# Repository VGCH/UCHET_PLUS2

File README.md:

## Проект устройства для интеграции счетчиков воды в системы умного дома

Принципиальная схема

Полное описание в статье на Хабр

[Ссылка на статью ](https://habr.com/ru/articles/827248/)

Если данный проект был вам полезен, то вы можете задонатить разработчику на оборудование. 

[Ссылка на донат](https://dalink.to/cyberex_tech)

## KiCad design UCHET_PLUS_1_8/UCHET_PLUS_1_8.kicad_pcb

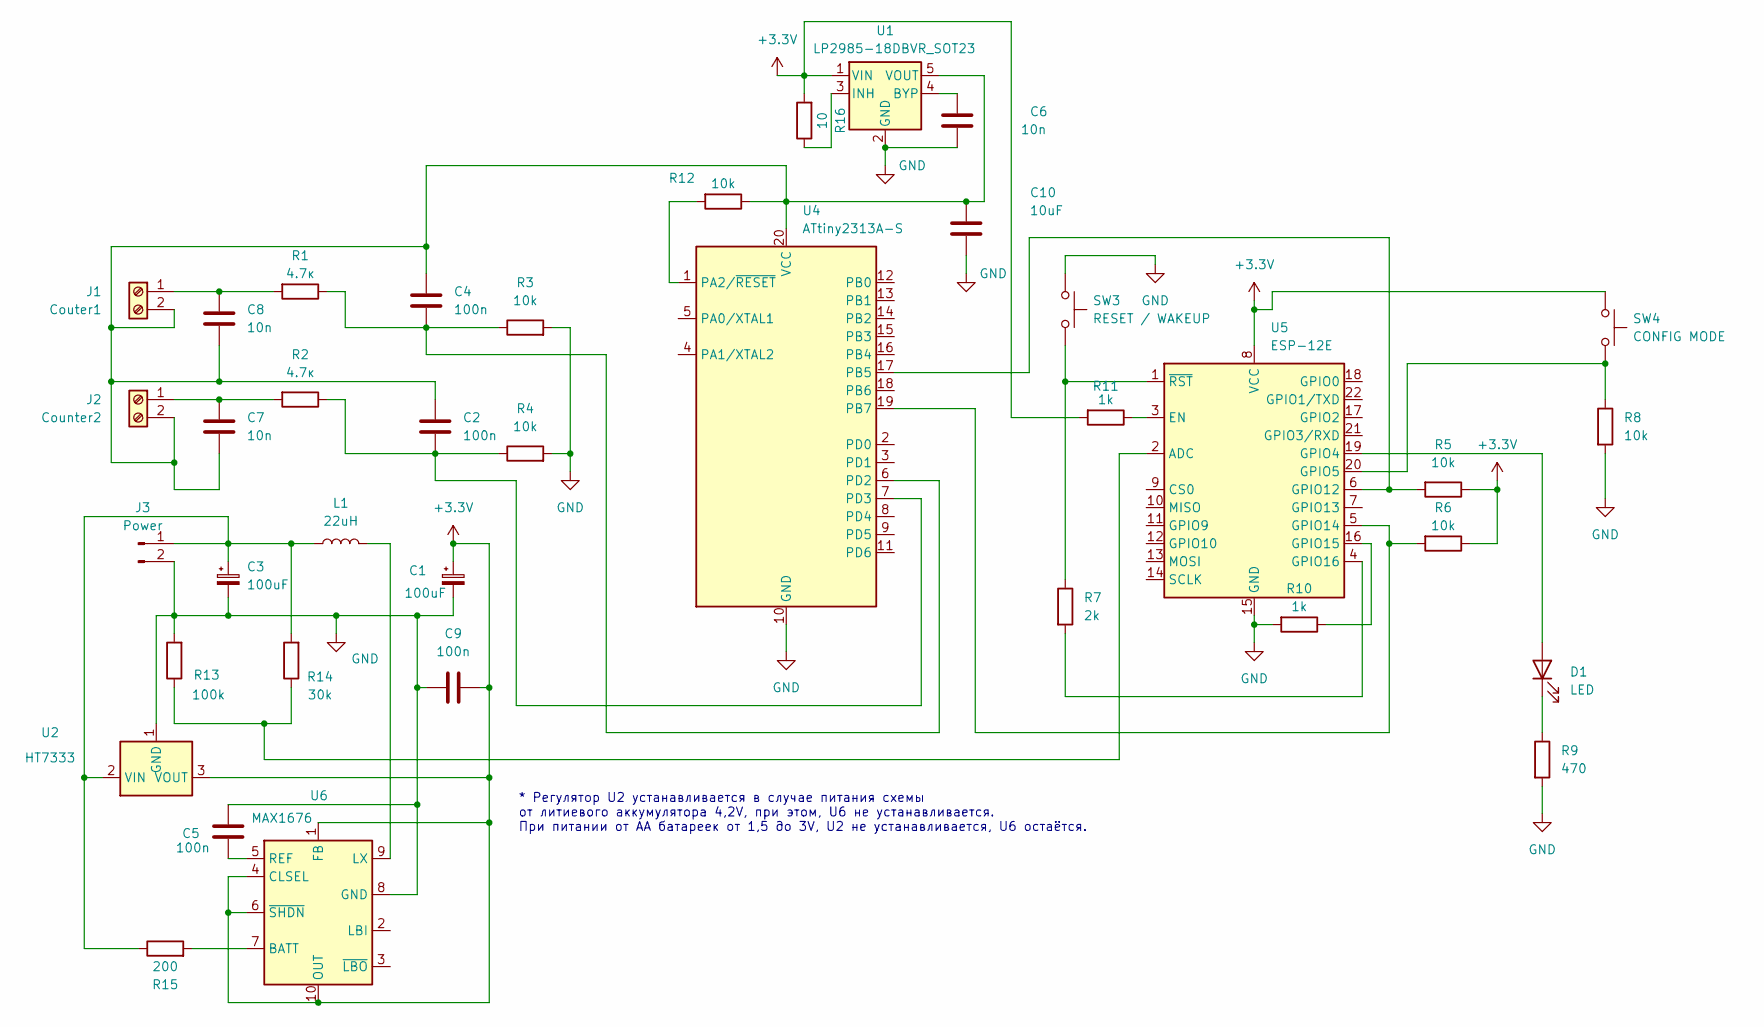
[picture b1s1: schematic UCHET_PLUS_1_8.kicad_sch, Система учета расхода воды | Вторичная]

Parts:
C1, C3: 100uF; CP_Elec_6.3x5.8
C2, C4, C5, C9: 100n; C_1206_3216Metric
C6, C7, C8: 10n; C_1206_3216Metric
C10: 10uF; C_1206_3216Metric
D1: LED; LED_D3.0mm_IRGrey
J1: Couter1; TerminalBlock_MetzConnect_Type101_RT01602HBWC_1x02_P5.08mm_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
J2: Counter2; TerminalBlock_MetzConnect_Type101_RT01602HBWC_1x02_P5.08mm_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
J3: Power; TerminalBlock_4Ucon_1x02_P3.50mm_Horizontal
L1: 22uH; L_1210_3225Metric
R1, R2: 4.7к; R_0805_2012Metric
R3, R4, R5, R6, R8, R12: 10k; R_0805_2012Metric
R7: 2k; R_0805_2012Metric
R9: 470; R_0805_2012Metric
R10, R11: 1k; R_0805_2012Metric
R13: 100k; R_0805_2012Metric
R14: 30k; R_0805_2012Metric
R15: 200; R_0805_2012Metric
R16: 10; R_0805_2012Metric
SW3: RESET / WAKEUP; SW_PUSH_6mm
SW4: CONFIG MODE; SW_PUSH_6mm
U1: LP2985-18DBVR_SOT23; SOT-23-5
U2: HT7333; SOT-23
U4: ATtiny2313A-S; SOIC-20W_7.5x12.8mm_P1.27mm
U5: ESP-12E
U6: MAX1676; MSOP-10-1EP_3x3mm_P0.5mm_EP2.2x3.1mm_Mask1.83x1.89mm_Therma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

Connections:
+3.3V: C1.1, C9.1, R5.1, R6.1, R11.2, R16.2, SW4.1, U1.1 (VIN), U2.3 (VOUT), U5.8 (VCC), U6.1 (FB), U6.4 (CLSEL), U6.6 (~SHDN), U6.10 (OUT), U6.11 (GND); also elsewhere on the board
GND: C1.2, C3.2, C5.1, C6.2, C9.2, C10.2, J3.2, R3.2, R4.2, R8.2, R9.2, R10.2, R13.2, SW3.1, U1.2 (GND), U2.1 (GND), U4.10 (GND), U5.15 (GND), U6.8 (GND); also elsewhere on the board
unnamed: D1.2 (A), U5.19 (GPIO4)
unnamed: D1.1 (K), R9.1
unnamed: C8.1, J1.1, R1.2
unnamed: C2.1, C4.1, C7.2, C8.2, C10.1, J1.2, J2.2, R12.1, U1.5 (VOUT), U4.20 (VCC)
unnamed: C7.1, J2.1, R2.2
unnamed: C3.1, J3.1, L1.1, R14.2, R15.1, U2.2 (VIN)
unnamed: C6.1, U1.4 (BYP)
unnamed: R16.1, U1.3 (INH)
unnamed: R12.2, U4.1 (PA2/~RESET)
unnamed: R5.2, U4.17 (PB5), U5.6 (GPIO12)
unnamed: R6.2, U4.19 (PB7), U5.5 (GPIO14)
unnamed: C4.2, R1.1, R3.1, U4.6 (PD2)
unnamed: C2.2, R2.1, R4.1, U4.7 (PD3)
unnamed: R13.1, R14.1, U5.2 (ADC)
unnamed: R11.1, U5.3 (EN)
unnamed: R8.1, SW4.2, U5.20 (GPIO5)
unnamed: R10.1, U5.16 (GPIO15)
unnamed: R7.2, U5.4 (GPIO16)
unnamed: R7.1, SW3.2, U5.1 (~RST)
unnamed: R15.2, U6.7 (BATT)
unnamed: L1.2, U6.9 (LX)
unnamed: C5.2, U6.5 (REF)

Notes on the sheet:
* Регулятор U2 устанавливается в случае питания схемы от литиевого аккумулятора 4,2V, при этом, U6 не устанавливается. При питании от AA батареек от 1,5 до 3V, U2 не устанавливается, U6 остаётся.

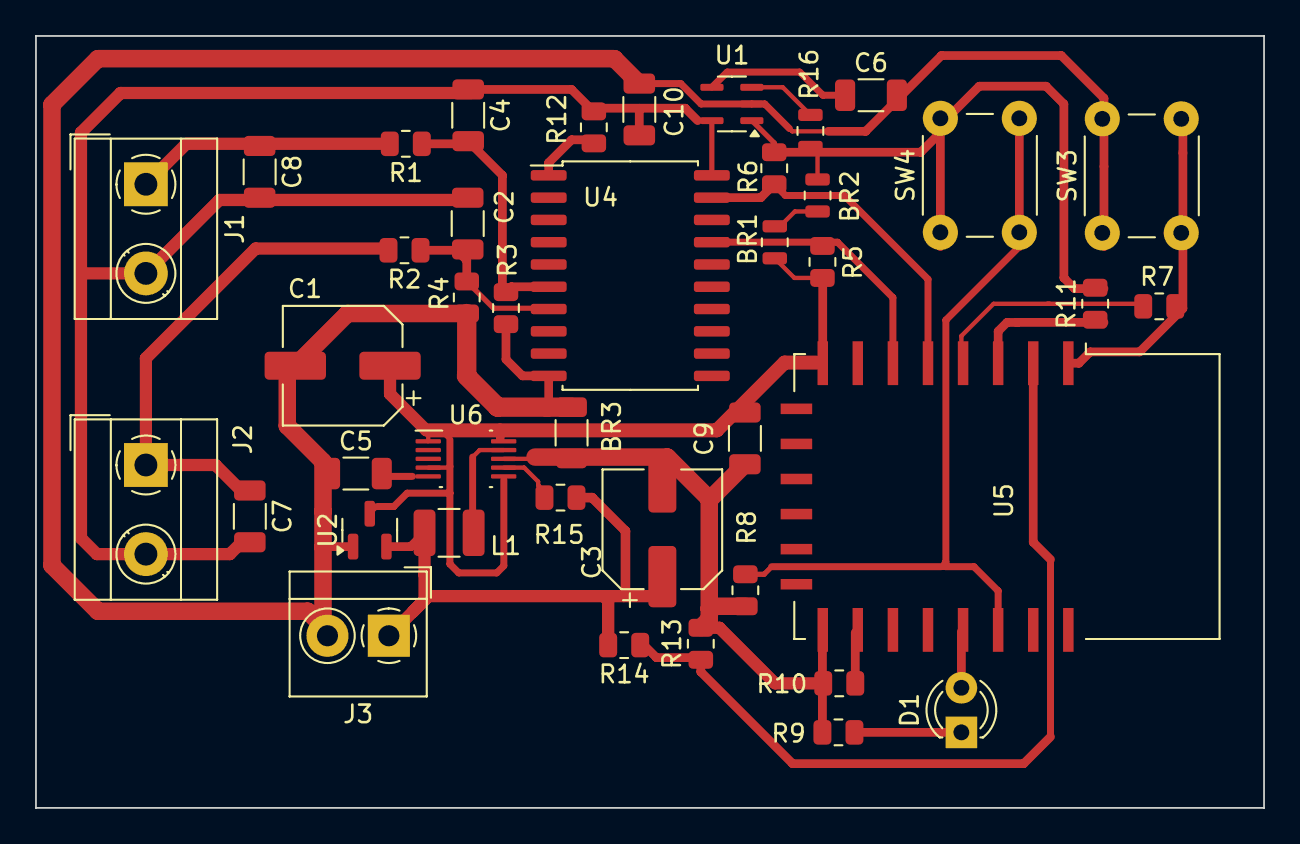
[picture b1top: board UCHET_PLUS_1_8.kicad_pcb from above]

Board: 2 copper layers, 70.0 x 44.0 mm, 41 parts (0 on the bottom side), 24 nets.

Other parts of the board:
BR1, BR2: R_0805_2012Metric
BR3: R_1206_3216Metric

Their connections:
+3.3V: BR1.1, BR1.2, BR2.1, BR2.2; also elsewhere on the board
GND: BR3.1, BR3.2; also elsewhere on the board

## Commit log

2024-07-10 Update README.md
    Update Read Me
